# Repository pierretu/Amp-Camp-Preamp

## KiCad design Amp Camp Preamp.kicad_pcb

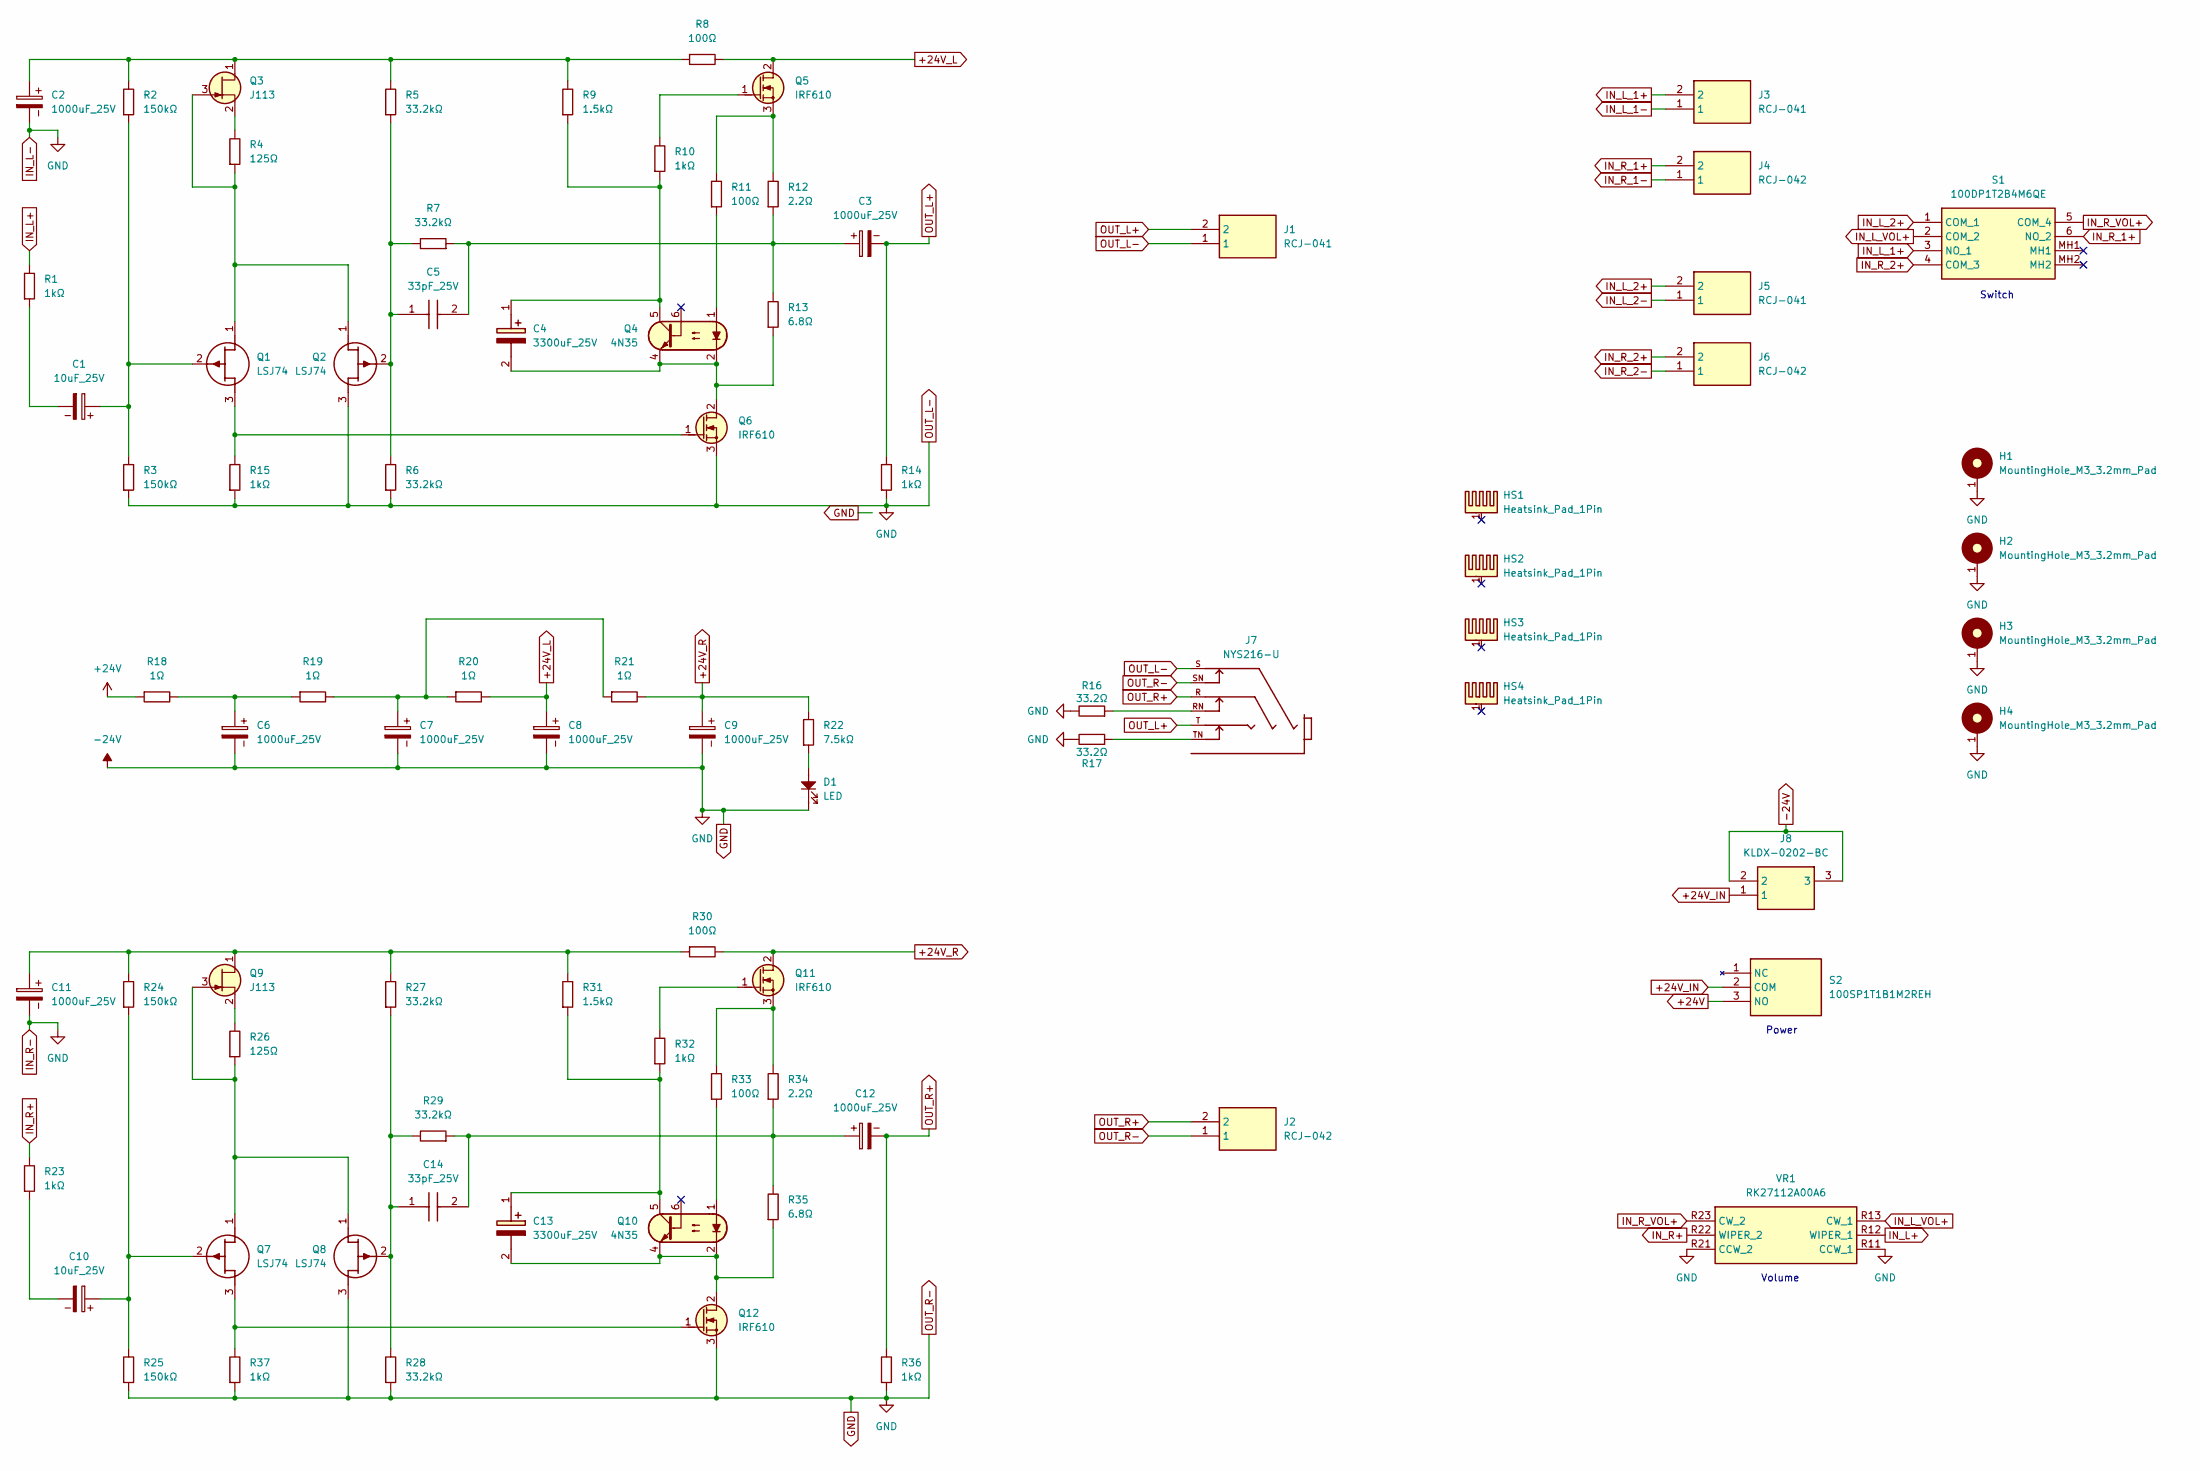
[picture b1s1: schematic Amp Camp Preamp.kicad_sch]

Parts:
C1, C10: 10uF_25V; CP_Radial_D5.0mm_P2.00mm
C2, C3, C6, C7, C8, C9, C11, C12: 1000uF_25V; CP_Radial_D13.0mm_P5.00mm
C4, C13: 3300uF_25V; CAPPRD750W80D1625H2700; Manufacturer_Part_Number UFW1E332MHD1TN
C5, C14: 33pF_25V; FKP2O100331D00JSSD; Manufacturer_Part_Number FKP2O100331D00JSSD
D1: LED; LED_D5.0mm
H1, H2, H3, H4: MountingHole_M3_3.2mm_Pad; MountingHole_3.2mm_Pad
HS1, HS2, HS3, HS4: Heatsink_Pad_1Pin; Heatsink_36.83x25.55mm_1xFixation3mm_Digikey_HS193-ND
J1, J3, J5: RCJ-041; RCJ041; Manufacturer_Part_Number RCJ-041
J2, J4, J6: RCJ-042; RCJ041; Manufacturer_Part_Number RCJ-042
J7: NYS216-U; NYS216-U_REAN_NYS216-U; PARTREV 2015.05.27
J8: KLDX-0202-BC; KLDX0202BC; Manufacturer_Part_Number KLDX-0202-BC
Q1, Q2, Q7, Q8: LSJ74; TO-92_Inline_Wide_DSG; Manufacturer_Part_Number LSJ74
Q3, Q9: J113; TO-92_Inline_Wide_DSG
Q4, Q10: 4N35; DIP-6_W7.62mm_LongPads
Q5, Q6, Q11, Q12: IRF610; TO-220-3_Vertical_GDS
R1, R10, R14, R15, R23, R32, R36, R37: 1kΩ; R_Axial_DIN0207_L6.3mm_D2.5mm_P10.16mm_Horizontal
R2, R3, R24, R25: 150kΩ; R_Axial_DIN0207_L6.3mm_D2.5mm_P10.16mm_Horizontal
R4, R26: 125Ω; R_Axial_DIN0207_L6.3mm_D2.5mm_P10.16mm_Horizontal
R5, R6, R7, R27, R28, R29: 33.2kΩ; R_Axial_DIN0207_L6.3mm_D2.5mm_P10.16mm_Horizontal
R8, R11, R30, R33: 100Ω; R_Axial_DIN0207_L6.3mm_D2.5mm_P10.16mm_Horizontal
R9, R31: 1.5kΩ; R_Axial_DIN0207_L6.3mm_D2.5mm_P10.16mm_Horizontal
R12, R34: 2.2Ω; R_Axial_DIN0207_L6.3mm_D2.5mm_P10.16mm_Horizontal
R13, R35: 6.8Ω; R_Axial_DIN0207_L6.3mm_D2.5mm_P10.16mm_Horizontal
R16, R17: 33.2Ω; R_Axial_DIN0207_L6.3mm_D2.5mm_P10.16mm_Horizontal
R18, R19, R20, R21: 1Ω; R_Axial_DIN0207_L6.3mm_D2.5mm_P10.16mm_Horizontal
R22: 7.5kΩ; R_Axial_DIN0207_L6.3mm_D2.5mm_P10.16mm_Horizontal
S1: 100DP1T2B4M6QE; Manufacturer_Part_Number 100DP1T2B4M6QE
S2: 100SP1T1B1M2REH; Manufacturer_Part_Number 100SP1T1B1M2REH
VR1: RK27112A00A6; Manufacturer_Part_Number RK27112A00A6

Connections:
+24V: R18.1, S2.3 (NO)
+24V_IN: J8.1, S2.2 (COM)
+24V_L: C8.1, Q5.2 (D), R8.2, R20.2
+24V_R: C9.1, Q11.2 (D), R21.2, R22.2, R30.2
-24V: C2.2, C6.2, C7.2, C8.2, C9.2, C11.2, D1.1, H1.1, H2.1, H3.1, H4.1, J1.1, J2.1, J7.S, J7.SN, J8.2, J8.3, Q2.3 (S), Q6.3 (S), Q8.3 (S), Q12.3 (S), R3.1, R6.1, R14.1, R15.1, R16.2, R17.2, R25.1, R28.1, R36.1, R37.1, VR1.R11 (CCW_1), VR1.R21 (CCW_2)
IN_L+: R1.2, VR1.R12 (WIPER_1)
IN_L_1+: J3.2, S1.3 (NO_1)
IN_L_1-: J3.1
IN_L_2+: J5.2, S1.1 (COM_1)
IN_L_2-: J5.1
IN_L_VOL+: S1.2 (COM_2), VR1.R13 (CW_1)
IN_R+: R23.2, VR1.R22 (WIPER_2)
IN_R_1+: J4.2, S1.6 (NO_2)
IN_R_1-: J4.1
IN_R_2+: J6.2, S1.4 (COM_3)
IN_R_2-: J6.1
IN_R_VOL+: S1.5 (COM_4), VR1.R23 (CW_2)
unnamed: C1.2, R1.1
unnamed: C3.1, C5.2, R7.1, R12.1, R13.2
unnamed: C4.1 (+), Q4.5, R9.1, R10.1
unnamed: C4.2 (-), Q4.2, Q4.4, Q6.2 (D), R13.1
unnamed: C6.1, R18.2, R19.1
unnamed: C7.1, R19.2, R20.1, R21.1
unnamed: C10.2, R23.1
unnamed: C12.1, C14.2, R29.1, R34.1, R35.2
unnamed: C13.1 (+), Q10.5, R31.1, R32.1
unnamed: C13.2 (-), Q10.2, Q10.4, Q12.2 (D), R35.1
unnamed: D1.2, R22.1
unnamed: J7.RN, R16.1
unnamed: J7.TN, R17.1
unnamed: Q1.1 (D), Q2.1 (D), Q3.3 (G), R4.1
unnamed: C1.1, Q1.2 (G), R2.1, R3.2
unnamed: Q1.3 (S), Q6.1 (G), R15.2
unnamed: C5.1, Q2.2 (G), R5.1, R6.2, R7.2
unnamed: C2.1, Q3.1 (D), R2.2, R5.2, R8.1, R9.2
unnamed: Q3.2 (S), R4.2
unnamed: Q4.1, R11.1
unnamed: Q5.1 (G), R10.2
unnamed: Q5.3 (S), R11.2, R12.2
unnamed: Q7.1 (D), Q8.1 (D), Q9.3 (G), R26.1
unnamed: C10.1, Q7.2 (G), R24.1, R25.2
unnamed: C14.1, Q8.2 (G), R27.1, R28.2, R29.2
unnamed: C11.1, Q9.1 (D), R24.2, R27.2, R30.1, R31.2
unnamed: Q9.2 (S), R26.2
unnamed: Q10.1, R33.1
unnamed: Q11.1 (G), R32.2
unnamed: Q11.3 (S), R33.2, R34.2
unnamed: Q7.3 (S), Q12.1 (G), R37.2
OUT_L+: C3.2, J1.2, J7.T, R14.2
OUT_R+: C12.2, J2.2, J7.R, R36.2

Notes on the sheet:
Power
Switch
Volume

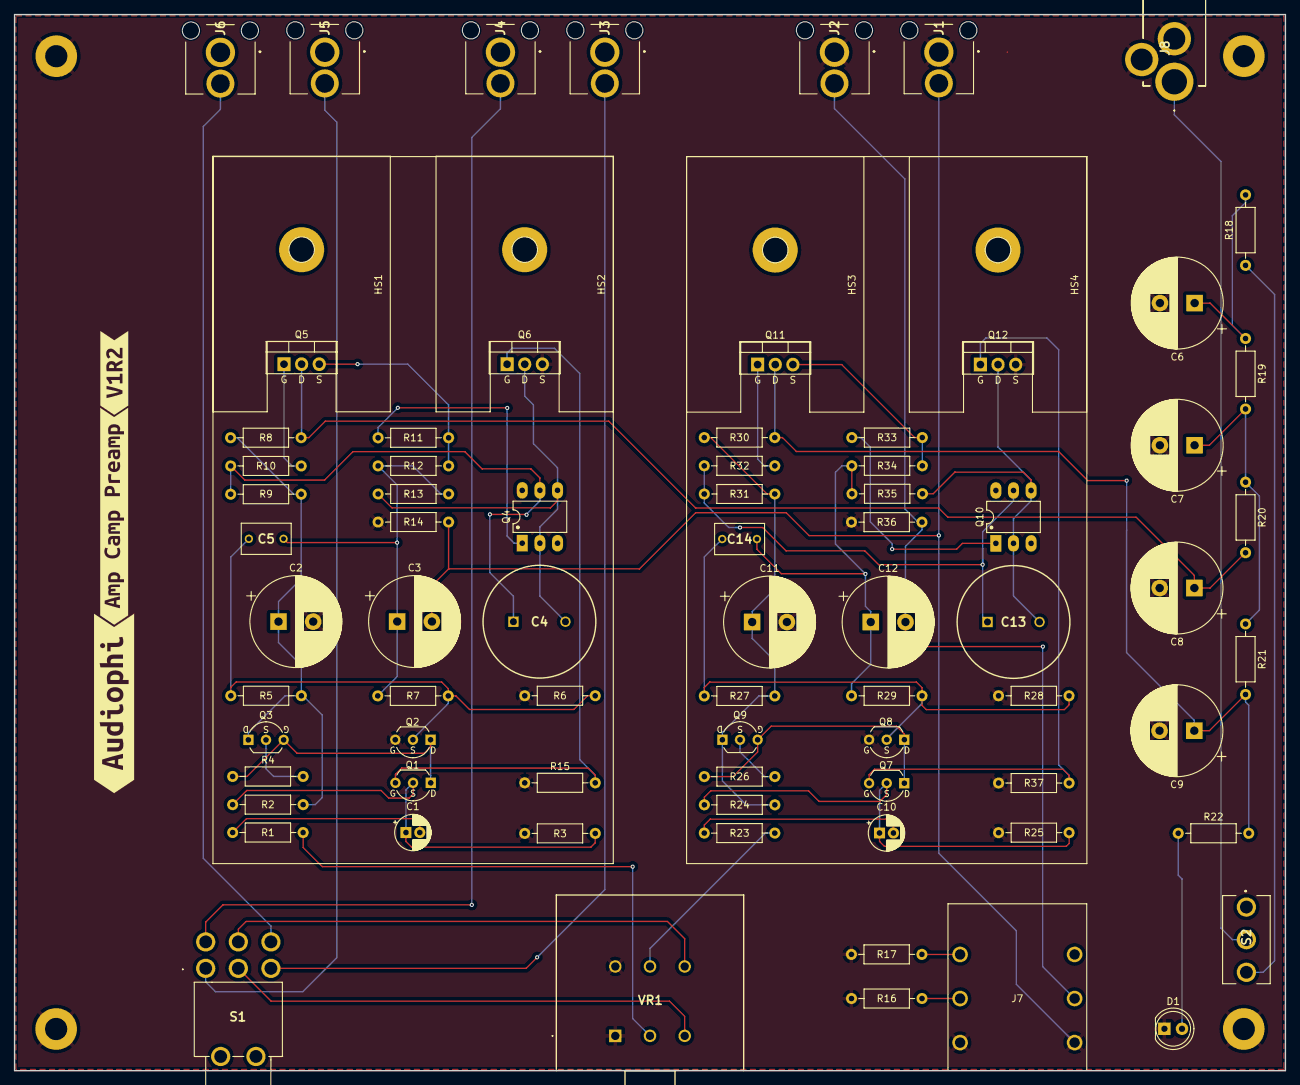
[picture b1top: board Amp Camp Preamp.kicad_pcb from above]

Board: 2 copper layers, 183.1 x 152.2 mm, 86 parts (0 on the bottom side), 46 nets.

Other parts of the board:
kibuzzard-675403C8: G***; kibuzzard-675403C8
kibuzzard-6754036E: G***; kibuzzard-6754036E
kibuzzard-6754048D: G***; kibuzzard-6754048D

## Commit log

2024-12-12 First release
